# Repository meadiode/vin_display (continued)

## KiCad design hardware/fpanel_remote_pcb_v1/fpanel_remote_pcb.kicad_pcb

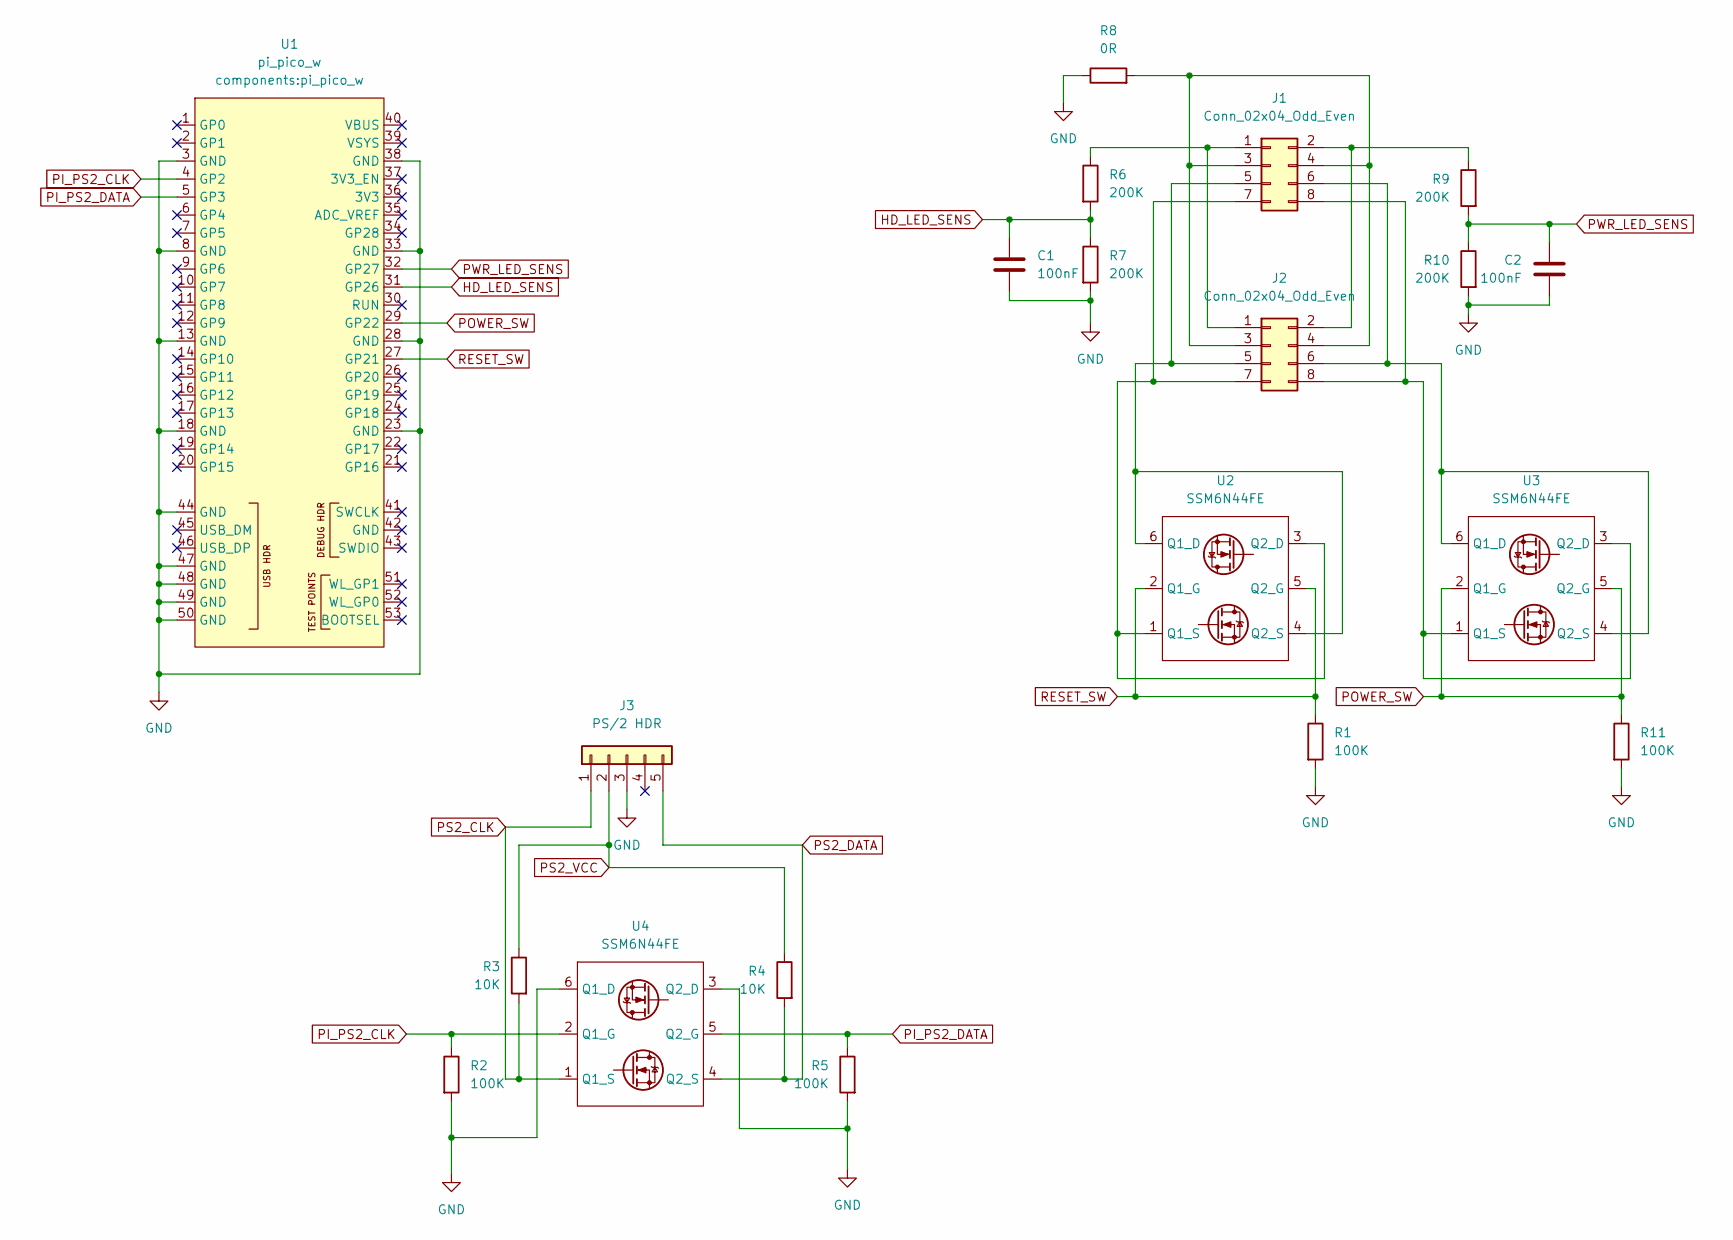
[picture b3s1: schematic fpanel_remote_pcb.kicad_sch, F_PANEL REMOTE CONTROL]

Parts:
C1, C2: 100nF; C_0603_1608Metric
J1, J2: Conn_02x04_Odd_Even; PinHeader_2x04_P2.54mm_Vertical
J3: PS/2 HDR; PinHeader_1x05_P2.54mm_Vertical
R1, R2, R5, R11: 100K; R_0603_1608Metric
R3, R4: 10K; R_0603_1608Metric
R6, R7, R9, R10: 200K; R_0603_1608Metric
R8: 0R; R_0603_1608Metric
U1: pi_pico_w
U2, U3, U4: SSM6N44FE; SOT-563

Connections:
GND: C1.2, C2.2, J3.3, R1.2, R2.2, R5.2, R7.2, R8.1, R10.2, R11.2, U1.3 (GND), U1.8 (GND), U1.13 (GND), U1.18 (GND), U1.23 (GND), U1.28 (GND), U1.33 (GND), U1.38 (GND), U1.44 (GND), U1.47 (GND), U1.48 (GND), U1.49 (GND), U1.50 (GND), U4.3 (Q2_D), U4.6 (Q1_D)
HD_LED_SENS: C1.1, R6.2, R7.1, U1.31 (GP26)
unnamed: J1.3, J1.4, J2.3, J2.4, R8.2
unnamed: J1.1, J2.1, R6.1
unnamed: J1.2, J2.2, R9.1
unnamed: J1.7, J2.7, U2.1 (Q1_S), U2.3 (Q2_D)
unnamed: J1.5, J2.5, U2.4 (Q2_S), U2.6 (Q1_D)
unnamed: J1.8, J2.8, U3.1 (Q1_S), U3.3 (Q2_D)
unnamed: J1.6, J2.6, U3.4 (Q2_S), U3.6 (Q1_D)
PI_PS2_CLK: R2.1, U1.4 (GP2), U4.2 (Q1_G)
PI_PS2_DATA: R5.1, U1.5 (GP3), U4.5 (Q2_G)
POWER_SW: R11.1, U1.29 (GP22), U3.2 (Q1_G), U3.5 (Q2_G)
PS2_CLK: J3.1, R3.2, U4.1 (Q1_S)
PS2_DATA: J3.5, R4.2, U4.4 (Q2_S)
PS2_VCC: J3.2, R3.1, R4.1
PWR_LED_SENS: C2.1, R9.2, R10.1, U1.32 (GP27)
RESET_SW: R1.1, U1.27 (GP21), U2.2 (Q1_G), U2.5 (Q2_G)

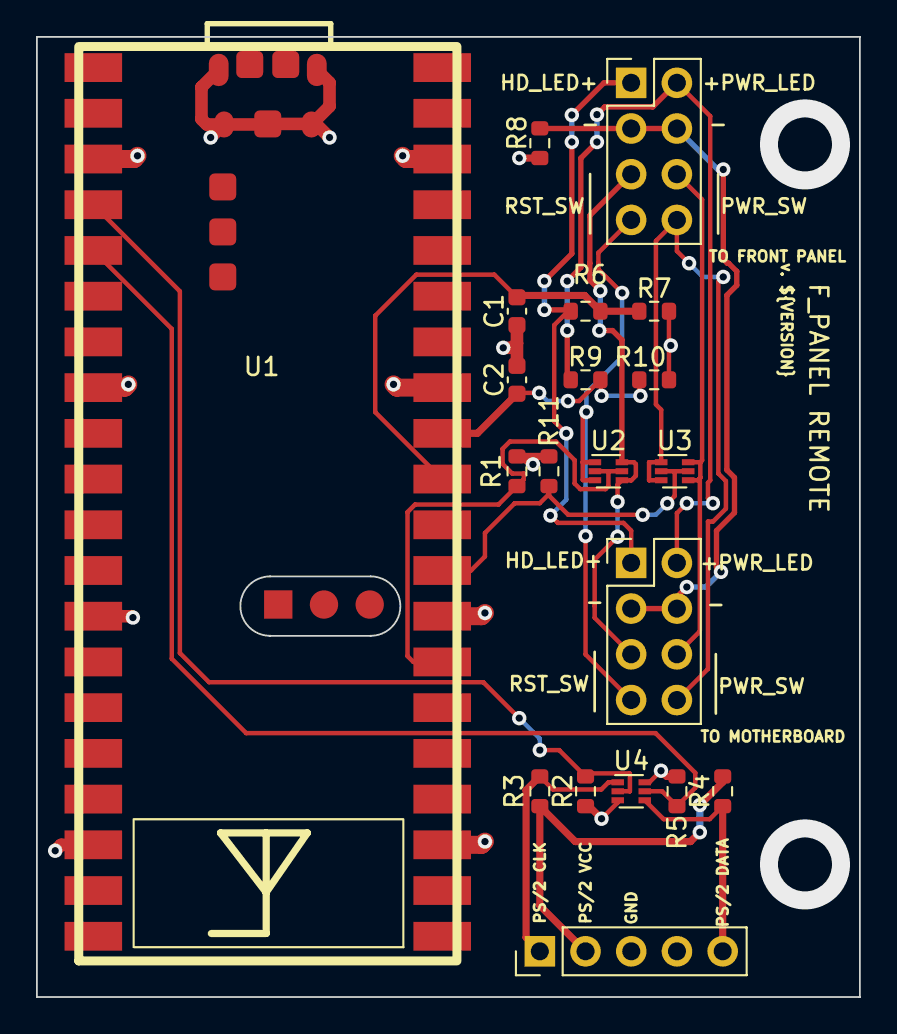
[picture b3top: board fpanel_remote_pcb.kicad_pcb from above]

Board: 2 copper layers, 45.7 x 53.3 mm, 20 parts (0 on the bottom side), 17 nets.

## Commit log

2023-01-26 basic FreeRTOS setup; http server; websocket; first version of PCB; fsdatagen.py; initial static web-files;
2023-01-26 add loicense
2023-01-27 ap mode experiments
2023-01-28 add svg graphics; websocket for the test server
2023-01-31 f-panel html/css
2023-02-24 functional web-ui
2023-03-02 +fpanel task; lwip and freertos tuning; buttons and leds do work
2023-03-03 websocket message handling improvements
2023-03-05 lwip tweaks; implement connection closing due to client timeout
2023-03-05 send pc uptime and temperature to client; more lwip tweaks
2023-03-06 disconnect current client if another connects
2023-03-08 print system run time stats; reduce stack sizes
2023-03-11 main.c clean up
2023-03-14 PIO deep dive; mdl2416c demo
2023-03-15 use a single mdl2416c to display messages
2023-03-15 some unexplainable sh
2023-03-16 now it works
2023-03-17 quick HDSP-2112 hook up and test
2023-03-19 drive hdsp-2112 with PIO and DMA
2023-03-19 display f_panel info on 3 hdsp2112
2023-03-31 display text on 8 mdl2416c displays
2023-04-02 clock display; ntp server synchromization; changed web interface;
2023-04-02 move sources to src; add demoboard1 kicad files; update readme
2023-04-02 readme typos
2023-04-09 initial work on schematics for mdl2416c display
2023-04-10 complete mdl2416c display schematics
2023-04-12 assign component footprints; basic pcb layout
2023-04-17 work on pcb layout
2023-04-21 +hdsp2000 display driver
2023-04-24 mdl2416c_x10 pcb routed
2023-04-25 mdl2416c_x10 pcb fixes/adjustments
2023-05-13 minor schematic fixes
2023-05-22 10x mdl2416c display fixes; buzzer pio
2023-06-24 knob/encoder pio; usb serial
2023-06-27 add klipper firmware files
2023-07-02 attempt to adapt klipper firmware
2023-07-02 remove irrelevant stuff; abandon klipper firmware adaptation
2023-07-10 implement simple protocol to communicate over usb serial cdc
2023-07-17 control buzzer with commands - queue and play sounds
2023-07-17 update schematic; add pdf
2023-07-18 update readme; add mdl2416c_x10 photo
2023-07-23 add display brightness control
2023-08-04 work on vin_display_hdsp2121_x6 schematics
2023-08-24 work on hdsp2112_x6 pcb
2023-10-12 minor pcb changes; add decoupling caps in mdl2416c_x10
2023-10-14 ignore kicad export files
2023-10-22 hdsp2112_x6 support
2023-10-24 fix knob for hdsp2112_x6
2024-01-28 add hdsp2112_x6 pdf and photo; fix encoder pins
2024-02-10 initial work on hdsp2000_x20 schematic
2024-02-17 route hdsp2000_x20 board
2024-02-19 hdsp2000_x20 pcb v1.0
2024-02-20 work on vqc10_x10 schematics
2024-02-21 routing vqc10_x10
2024-02-25 rewrite hdsp2112 PIO
2024-02-26 route vqc10_x10 board
2024-03-03 add interface UART
2024-03-03 slightly optimize knob PIO program
2024-03-08 hdsp2000_x20 minor changes
2024-03-23 minor fixes in vqc10_x10 and hdsp2000_x20 pcb/schematics
2024-03-30 add vqc10 module; drive vqc10_x10 with PIO and DMA; add transposed font
2024-05-26 work on hdsp2000_x20 software; graphic mode/double buffering
